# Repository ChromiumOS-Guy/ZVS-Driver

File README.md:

# ZVS-Driver
A ZVS Driver (1-Layer) PCB I Designed so I can use a PCB instead of making a mess of wires

# Part List:
Part .No | Buy Link
------------- | ------------- 
691137710002 | https://www.digikey.co.il/en/products/detail/w%C3%BCrth-elektronik/691137710002/6644051
B32654A6105K000 | https://www.digikey.co.il/en/products/detail/epcos-tdk-electronics/B32654A6105K000/2269405
PR02000204700JR500 | https://www.digikey.co.il/en/products/detail/vishay-beyschlag-draloric-bc-components/PR02000204700JR500/596196
CF14JT10K0 | https://www.digikey.co.il/en/products/detail/stackpole-electronics-inc/CF14JT10K0/1741265
CF14JT1K00 | https://www.digikey.co.il/en/products/detail/stackpole-electronics-inc/CF14JT1K00/1741314
HLMP-3601 | https://www.digikey.co.il/en/products/detail/broadcom-limited/HLMP-3601/637604
1N5246B | https://www.digikey.co.il/en/products/detail/onsemi/1N5246B/977606
HCTI-100-7.0 | https://www.digikey.co.il/en/products/detail/signal-transformer/HCTI-100-7-0/7362979
IRFP260NPBF | https://www.digikey.co.il/he/products/detail/infineon-technologies/IRFP260NPBF/811623?s=N4IgTCBcDaIJICUBiAFMA2ADAORAXQF8g

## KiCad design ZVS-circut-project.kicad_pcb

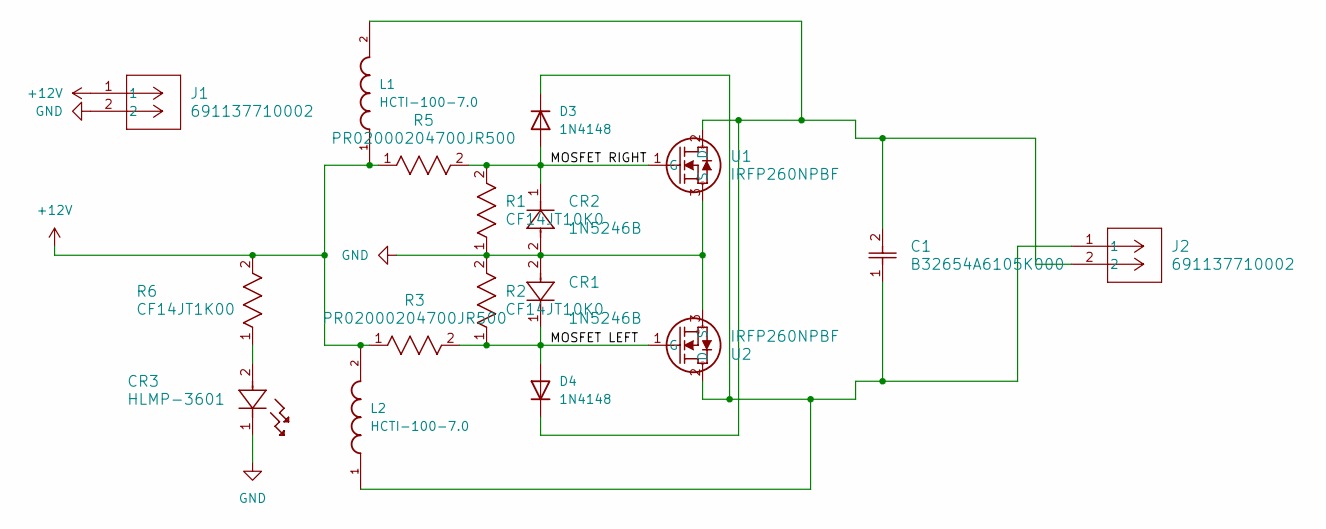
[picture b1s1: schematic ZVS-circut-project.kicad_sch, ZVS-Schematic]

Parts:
C1: B32654A6105K000; CAP_B32654A-27.5-13.5x23x31.5_TDK
CR1, CR2: 1N5246B; AFL-W2C8.9D
CR3: HLMP-3601; HMLP_1&slash_3_AVA
D3, D4: 1N4148; D_DO-35_SOD27_P7.62mm_Horizontal
J1, J2: 691137710002; CONN2_710002_WRE
L1, L2: HCTI-100-7.0; IND_HCTI-68-7.7; PARTREV N/A
R1, R2: CF14JT10K0; STA_CF14_STP
R3, R5: PR02000204700JR500; PR02_VIS
R6: CF14JT1K00; STA_CF14_STP
U1, U2: IRFP260NPBF; PG-TO247-3-46_INF

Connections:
+12V: J1.1, L1.1, L2.2, R3.1, R5.1, R6.2
/MOSFET LEFT: CR1.1, D4.2 (A), R2.1, R3.2, U2.1 (G)
/MOSFET RIGHT: CR2.1, D3.2 (A), R1.2, R5.2, U1.1 (G)
GND: CR1.2, CR2.2, CR3.1, J1.2, R1.1, R2.2, U1.3 (S), U2.3 (S)
unnamed: CR3.2, R6.1
unnamed: C1.1, D3.1 (K), J2.1, L2.1, U2.2 (D)
unnamed: C1.2, D4.1 (K), J2.2, L1.2, U1.2 (D)

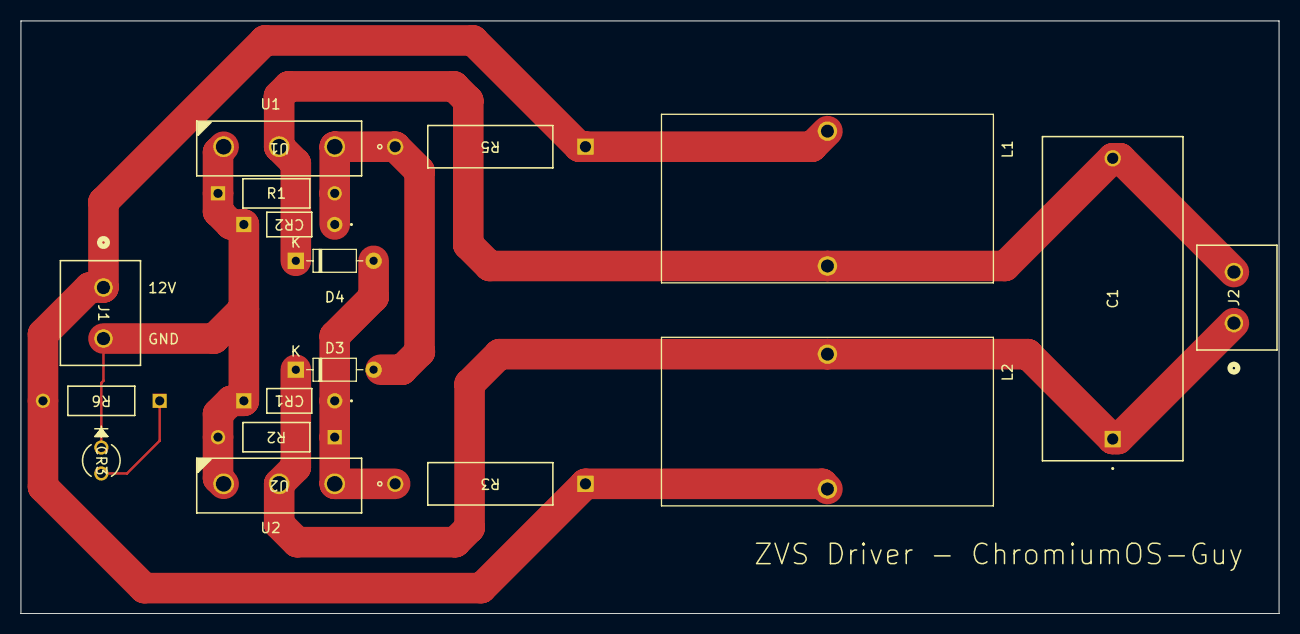
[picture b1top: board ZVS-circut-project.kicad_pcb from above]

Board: 2 copper layers, 123.2 x 58.0 mm, 17 parts (0 on the bottom side), 7 nets.

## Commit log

2024-03-22 Add files via upload
    first upload yay
2024-03-22 Update README.md
    spelling sucks
2024-03-22 Update README.md
    V1.0.2 has it correct
